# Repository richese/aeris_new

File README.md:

# aeris_new
aeris mutirobtics system

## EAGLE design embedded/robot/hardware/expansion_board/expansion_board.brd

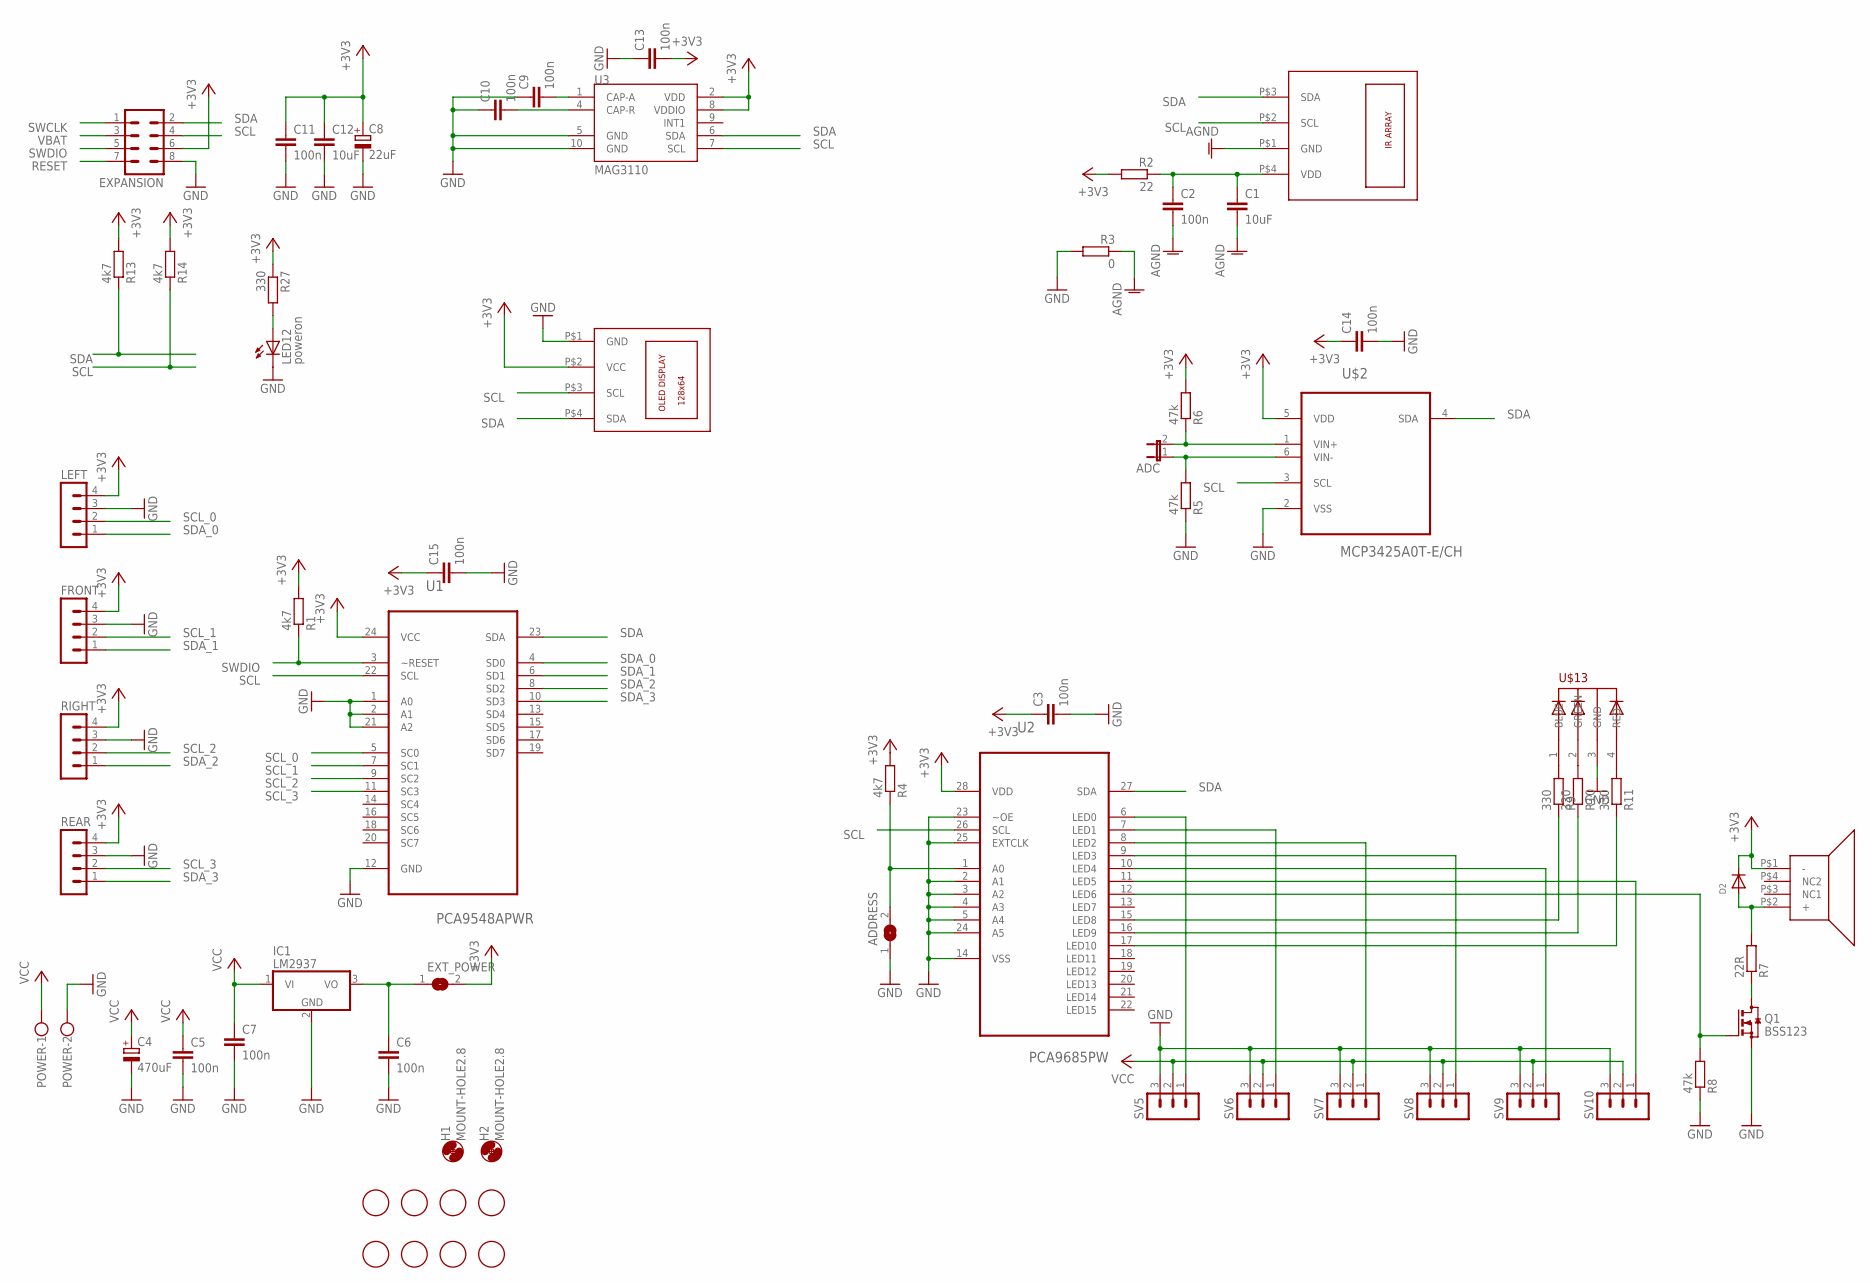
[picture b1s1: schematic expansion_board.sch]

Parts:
ADC: JP1E; JP1
ADDRESS: SJ
C1, C12: 10uF; C0805
C2, C3, C5, C6, C7, C9, C10, C11, C13, C14, C15: 100n; C0805
C4: 470uF; 153CLV-1012
C8: 22uF; 153CLV-0505
D2: DIODE_SOD-123FL; SOD-123FL
EXPANSION: MA04-2
EXT_POWER: SJ
FRONT: MA04-1
H1, H2: MOUNT-HOLE2.8; 2,8
IC1: LM2937; TO263-3
LED12: poweron; CHIPLED_1206
LEFT: MA04-1
POWER: W237-102
Q1: BSS123; SOT23
R1, R4, R13, R14: 4k7; M0805
R2: 22; M0805
R3: 0; M0805
R5, R6, R8: 47k; M0805
R7: 22R; M0805
R9, R10, R11, R27: 330; M0805
REAR: MA04-1
RIGHT: MA04-1
SV5, SV6, SV7, SV8, SV9, SV10: MA03-1
U1: PCA9548APWR; SOP65P640X120-24N
U2: PCA9685PW; SOP65P640X110-28N
U3: MAG3110; DFN-10
U$1: MLX90621
U$2: MCP3425A0T-E/CH; SOT95P270X145-6N
U$3: SPEAKER_KAAG15008C; KAAG15008C
U$4: OLED_DISPLAY_096_INCH
U$5, U$6, U$7, U$8, U$9, U$10, U$11, U$12: FIDUCIAL; FIDUCIAL_1MM
U$13: 5MMRGBLED; LED5MMRGB

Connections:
+3V3: C3.1, C8.+, C11.1, C12.1, C13.2, C14.1, C15.1, D2.C, EXPANSION.6, EXT_POWER.2, FRONT.4, LEFT.4, R1.2, R2.2, R4.2, R6.2, R13.2, R14.2, R27.1, REAR.4, RIGHT.4, U1.24 (VCC), U2.28 (VDD), U3.2 (VDD), U3.8 (VDDIO), U$2.5 (VDD), U$3.P$1 (-), U$4.P$2 (VCC)
AGND: C1.2, C2.2, R3.1, U$1.P$1 (GND)
GND: ADDRESS.1, C3.2, C4.-, C5.2, C6.2, C7.2, C8.-, C9.1, C10.1, C11.2, C12.2, C13.1, C14.2, C15.2, EXPANSION.8, FRONT.3, IC1.2 (GND), LED12.C, LEFT.3, POWER.2, Q1.2 (S), R3.2, R5.1, R8.1, REAR.3, RIGHT.3, SV5.3, SV6.3, SV7.3, SV8.3, SV9.3, SV10.3, U1.1 (A0), U1.2 (A1), U1.12 (GND), U1.21 (A2), U2.2 (A1), U2.3 (A2), U2.4 (A3), U2.5 (A4), U2.14 (VSS), U2.23 (~OE), U2.24 (A5), U2.25 (EXTCLK), U3.5 (GND), U3.10 (GND), U$2.2 (VSS), U$4.P$1 (GND), U$13.3 (GND)
unnamed: C1.1, C2.1, R2.1, U$1.P$4 (VDD)
unnamed: SV5.1, U2.6 (LED0)
unnamed: SV6.1, U2.7 (LED1)
unnamed: SV7.1, U2.8 (LED2)
unnamed: SV8.1, U2.9 (LED3)
unnamed: SV9.1, U2.10 (LED4)
unnamed: SV10.1, U2.11 (LED5)
unnamed: C6.1, EXT_POWER.1, IC1.3 (VO)
unnamed: ADDRESS.2, R4.1, U2.1 (A0)
unnamed: C9.2, U3.1 (CAP-A)
unnamed: C10.2, U3.4 (CAP-R)
unnamed: ADC.1, R5.2, U$2.6 (VIN-)
unnamed: ADC.2, R6.1, U$2.1 (VIN+)
unnamed: R9.2, U$13.1 (BLUE)
unnamed: Q1.1 (G), R8.2, U2.12 (LED6)
unnamed: Q1.3 (D), R7.1
unnamed: D2.A, R7.2, U$3.P$2 (+)
unnamed: R11.2, U$13.4 (RED)
unnamed: R10.2, U$13.2 (GREEN)
unnamed: LED12.A, R27.2
unnamed: R9.1, U2.15 (LED8)
unnamed: R10.1, U2.16 (LED9)
unnamed: R11.1, U2.17 (LED10)
RESET: EXPANSION.7
SCL: EXPANSION.4, R14.1, U1.22 (SCL), U2.26 (SCL), U3.7 (SCL), U$1.P$2 (SCL), U$2.3 (SCL), U$4.P$3 (SCL)
SCL_0: LEFT.2, U1.5 (SC0)
SCL_1: FRONT.2, U1.7 (SC1)
SCL_2: RIGHT.2, U1.9 (SC2)
SCL_3: REAR.2, U1.11 (SC3)
SDA: EXPANSION.2, R13.1, U1.23 (SDA), U2.27 (SDA), U3.6 (SDA), U$1.P$3 (SDA), U$2.4 (SDA), U$4.P$4 (SDA)
SDA_0: LEFT.1, U1.4 (SD0)
SDA_1: FRONT.1, U1.6 (SD1)
SDA_2: RIGHT.1, U1.8 (SD2)
SDA_3: REAR.1, U1.10 (SD3)
SWCLK: EXPANSION.1
SWDIO: EXPANSION.5, R1.1, U1.3 (~RESET)
VBAT: EXPANSION.3
VCC: C4.+, C5.1, C7.1, IC1.1 (VI), POWER.1, SV5.2, SV6.2, SV7.2, SV8.2, SV9.2, SV10.2

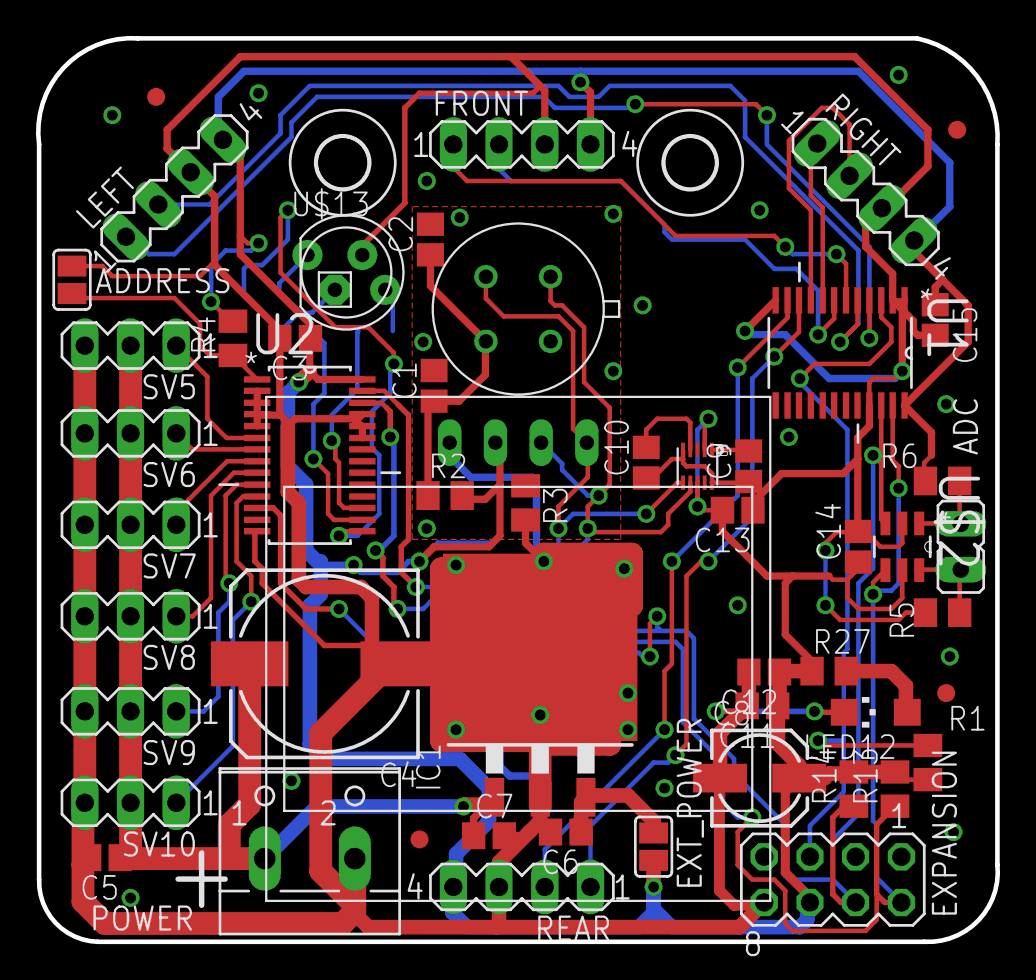
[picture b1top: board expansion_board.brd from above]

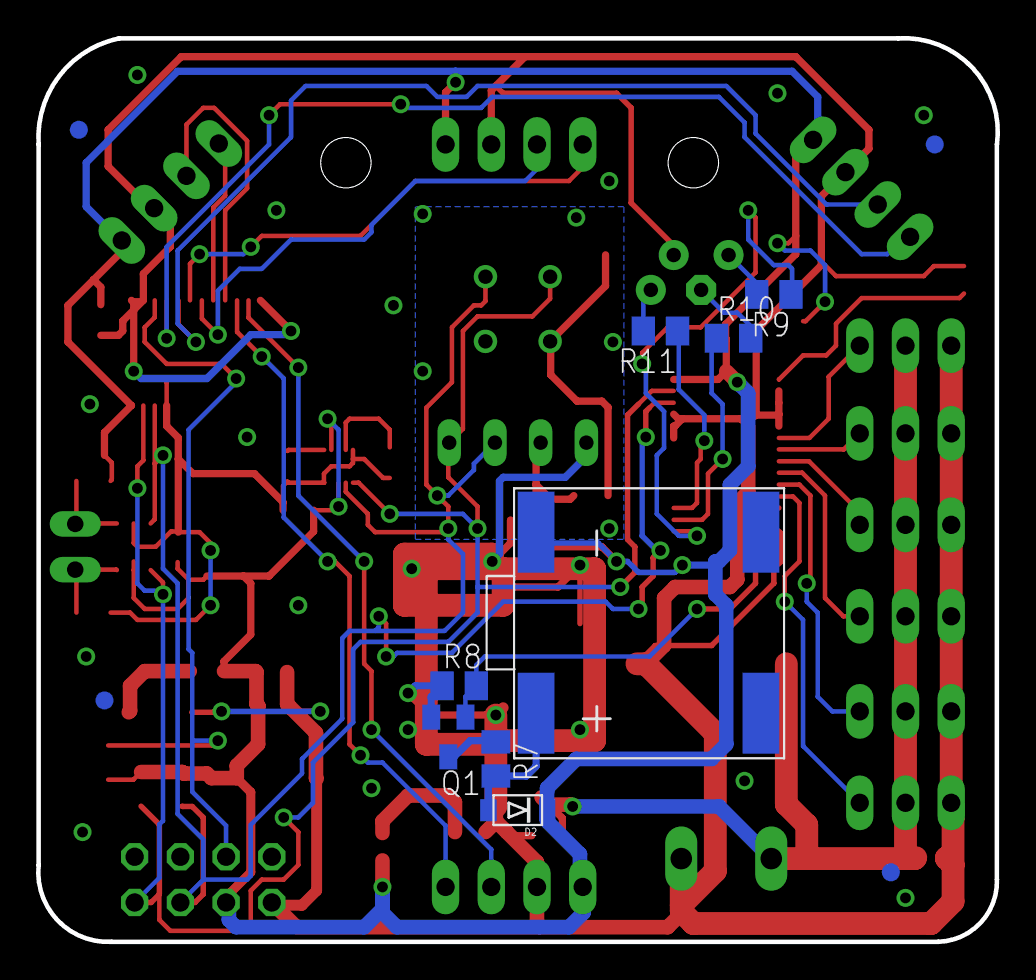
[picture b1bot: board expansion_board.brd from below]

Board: 2 copper layers, 53.3 x 50.2 mm, 66 parts (12 on the bottom side), 38 nets.

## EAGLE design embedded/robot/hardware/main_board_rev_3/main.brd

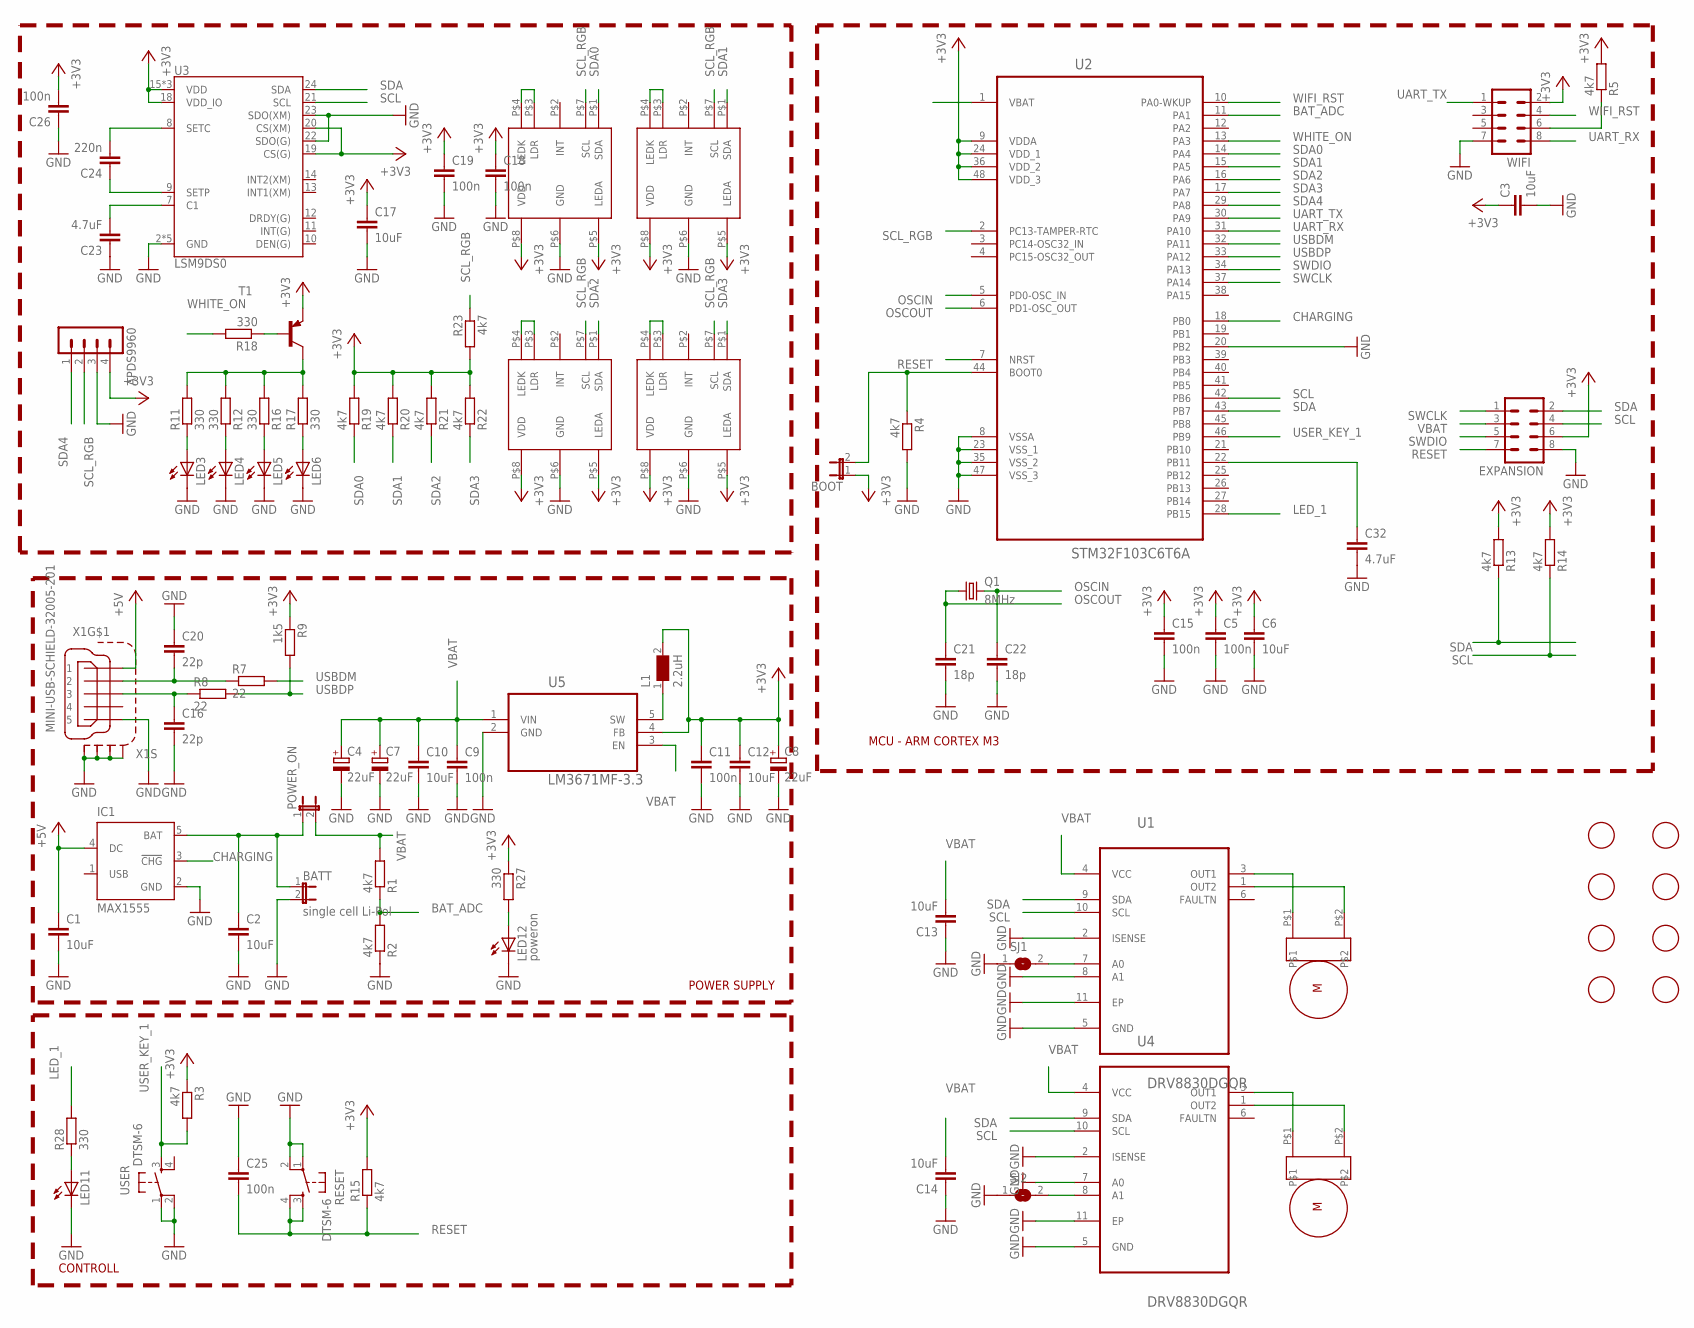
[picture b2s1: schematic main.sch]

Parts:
APDS9960: MA04-1
BATT: single cell Li-Pol; JP1
BOOT: JP1E; JP1
C1, C2, C3, C6, C10, C12, C13, C14, C17: 10uF; C0805
C4, C7, C8: 22uF; 153CLV-0505
C5, C9, C11, C15, C18, C19, C25, C26: 100n; C0805
C16, C20: 22p; C0805
C21, C22: 18p; C0805
C23, C32: 4.7uF; C0805
C24: 220n; C0805
EXPANSION: MA04-2
IC1: MAX1555; SOT23-5L
L1: 2.2uH; WE-LQ_M
LED3, LED4, LED5, LED6, LED11: LEDCHIPLED_1206; CHIPLED_1206
LED12: poweron; CHIPLED_1206
POWER_ON: JP1E; JP1
Q1: 8MHz; CTS406
R1, R2, R4, R5, R13, R14, R15, R19, R20, R21, R22, R23: 4k7; M0805
R3: 4k7; M1206
R7, R8: 22; M0805
R9: 1k5; M0805
R11, R12, R16, R17, R18, R27, R28: 330; M0805
RESET: DTSM-6
SJ1, SJ2: SJ
T1: BC857A-PNP-SOT23-BEC; SOT23-BEC
U1, U4: DRV8830DGQR; SOP65P640X110-15N
U2: STM32F103C6T6A; QFP50P900X900X160-48N
U3: LSM9DS0; LGA-24
U5: LM3671MF-3.3; SOT95P284X122-5N
U$1, U$2, U$3, U$4: APDS9950
U$5, U$6: MICRO_METAL_GEAR_MOTOR
U$9, U$10, U$11, U$12, U$13, U$14, U$15, U$16: FIDUCIAL; FIDUCIAL_1MM
USER: DTSM-6
WIFI: MA04-2
X1: MINI-USB-SCHIELD-32005-201; 32005-201

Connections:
+3V3: APDS9960.4, BOOT.1, C3.1, C5.1, C6.1, C8.+, C11.1, C12.1, C15.1, C17.1, C18.1, C19.1, C26.2, EXPANSION.6, L1.2, R3.1, R5.2, R9.1, R13.2, R14.2, R15.2, R19.2, R20.2, R21.2, R22.2, R23.2, R27.1, T1.E, U2.9 (VDDA), U2.24 (VDD_1), U2.36 (VDD_2), U2.48 (VDD_3), U3.15 (VDD), U3.16 (VDD), U3.17 (VDD), U3.18 (VDD_IO), U3.19 (CS(G)), U3.20 (CS(XM)), U5.4 (FB), U$1.P$5 (LEDA), U$1.P$8 (VDD), U$2.P$5 (LEDA), U$2.P$8 (VDD), U$3.P$5 (LEDA), U$3.P$8 (VDD), U$4.P$5 (LEDA), U$4.P$8 (VDD), WIFI.2
+5V: C1.1, IC1.4 (DC), X1.1
BAT_ADC: R1.1, R2.2, U2.11 (PA1)
CHARGING: IC1.3 (!CHG), U2.18 (PB0)
GND: APDS9960.3, BATT.2, C1.2, C2.2, C3.2, C4.-, C5.2, C6.2, C7.-, C8.-, C9.2, C10.2, C11.2, C12.2, C13.1, C14.1, C15.2, C16.2, C17.2, C18.2, C19.2, C20.1, C21.2, C22.2, C23.1, C25.1, C26.1, C32.2, EXPANSION.8, IC1.2 (GND), LED3.C, LED4.C, LED5.C, LED6.C, LED11.C, LED12.C, R2.1, R4.2, RESET.1, RESET.2, SJ1.1, SJ2.1, U1.2 (ISENSE), U1.5 (GND), U1.8 (A1), U1.11 (EP), U2.8 (VSSA), U2.20 (PB2), U2.23 (VSS_1), U2.35 (VSS_2), U2.47 (VSS_3), U3.2 (GND), U3.3 (GND), U3.4 (GND), U3.5 (GND), U3.6 (GND), U3.22 (SDO(G)), U3.23 (SDO(XM)), U4.2 (ISENSE), U4.5 (GND), U4.7 (A0), U4.11 (EP), U5.2 (GND), U$1.P$6 (GND), U$2.P$6 (GND), U$3.P$6 (GND), U$4.P$6 (GND), USER.1, USER.2, WIFI.7, X1.5, X1.M1 (S1), X1.M2 (S2), X1.M3 (S3), X1.M4 (S4)
LED_1: R28.2, U2.28 (PB15)
unnamed: R5.1, WIFI.6
unnamed: BATT.1, C2.1, IC1.5 (BAT), POWER_ON.1
unnamed: U1.1 (OUT2), U$5.P$2
unnamed: U1.3 (OUT1), U$5.P$1
unnamed: U4.1 (OUT2), U$6.P$2
unnamed: C23.2, U3.7 (C1)
unnamed: C24.2, U3.8 (SETC)
unnamed: U4.3 (OUT1), U$6.P$1
unnamed: L1.1, U5.5 (SW)
unnamed: C24.1, U3.9 (SETP)
unnamed: C32.1, U2.22 (PB11)
unnamed: LED3.A, R11.1
unnamed: BOOT.2, R4.1, U2.44 (BOOT0)
unnamed: U$1.P$3 (LDR), U$1.P$4 (LEDK)
unnamed: U$2.P$3 (LDR), U$2.P$4 (LEDK)
unnamed: U$3.P$3 (LDR), U$3.P$4 (LEDK)
unnamed: U$4.P$3 (LDR), U$4.P$4 (LEDK)
unnamed: SJ1.2, U1.7 (A0)
unnamed: LED4.A, R12.1
unnamed: LED12.A, R27.2
unnamed: LED5.A, R16.1
unnamed: LED6.A, R17.1
unnamed: R11.2, R12.2, R16.2, R17.2, T1.C
unnamed: R18.1, T1.B
unnamed: SJ2.2, U4.8 (A1)
unnamed: LED11.A, R28.1
unnamed: C20.2, R7.1, X1.2
unnamed: C16.1, R8.1, X1.3
NC: U2.1 (VBAT)
OSCIN: C22.1, Q1.3 (2), U2.5 (PD0-OSC_IN)
OSCOUT: C21.1, Q1.1, U2.6 (PD1-OSC_OUT)
RESET: C25.2, EXPANSION.7, R15.1, RESET.3, RESET.4, U2.7 (NRST)
SCL: EXPANSION.4, R14.1, U1.10 (SCL), U2.42 (PB6), U3.21 (SCL), U4.10 (SCL)
SCL_RGB: APDS9960.2, R23.1, U2.2 (PC13-TAMPER-RTC), U$1.P$7 (SCL), U$2.P$7 (SCL), U$3.P$7 (SCL), U$4.P$7 (SCL)
SDA: EXPANSION.2, R13.1, U1.9 (SDA), U2.43 (PB7), U3.24 (SDA), U4.9 (SDA)
SDA0: R19.1, U2.14 (PA4), U$1.P$1 (SDA)
SDA1: R20.1, U2.15 (PA5), U$2.P$1 (SDA)
SDA2: R21.1, U2.16 (PA6), U$3.P$1 (SDA)
SDA3: R22.1, U2.17 (PA7), U$4.P$1 (SDA)
SDA4: APDS9960.1, U2.29 (PA8)
SWCLK: EXPANSION.1, U2.37 (PA14)
SWDIO: EXPANSION.5, U2.34 (PA13)
UART_RX: U2.31 (PA10), WIFI.8
UART_TX: U2.30 (PA9), WIFI.1
USBDM: R7.2, U2.32 (PA11)
USBDP: R8.2, R9.2, U2.33 (PA12)
USER_KEY_1: R3.2, U2.46 (PB9), USER.3
VBAT: C4.+, C7.+, C9.1, C10.1, C13.2, C14.2, EXPANSION.3, POWER_ON.2, R1.2, U1.4 (VCC), U4.4 (VCC), U5.1 (VIN), U5.3 (EN)
WHITE_ON: R18.2, U2.13 (PA3)
WIFI_RST: U2.10 (PA0-WKUP), WIFI.4

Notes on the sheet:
POWER SUPPLY
CONTROLL
MCU - ARM CORTEX M3

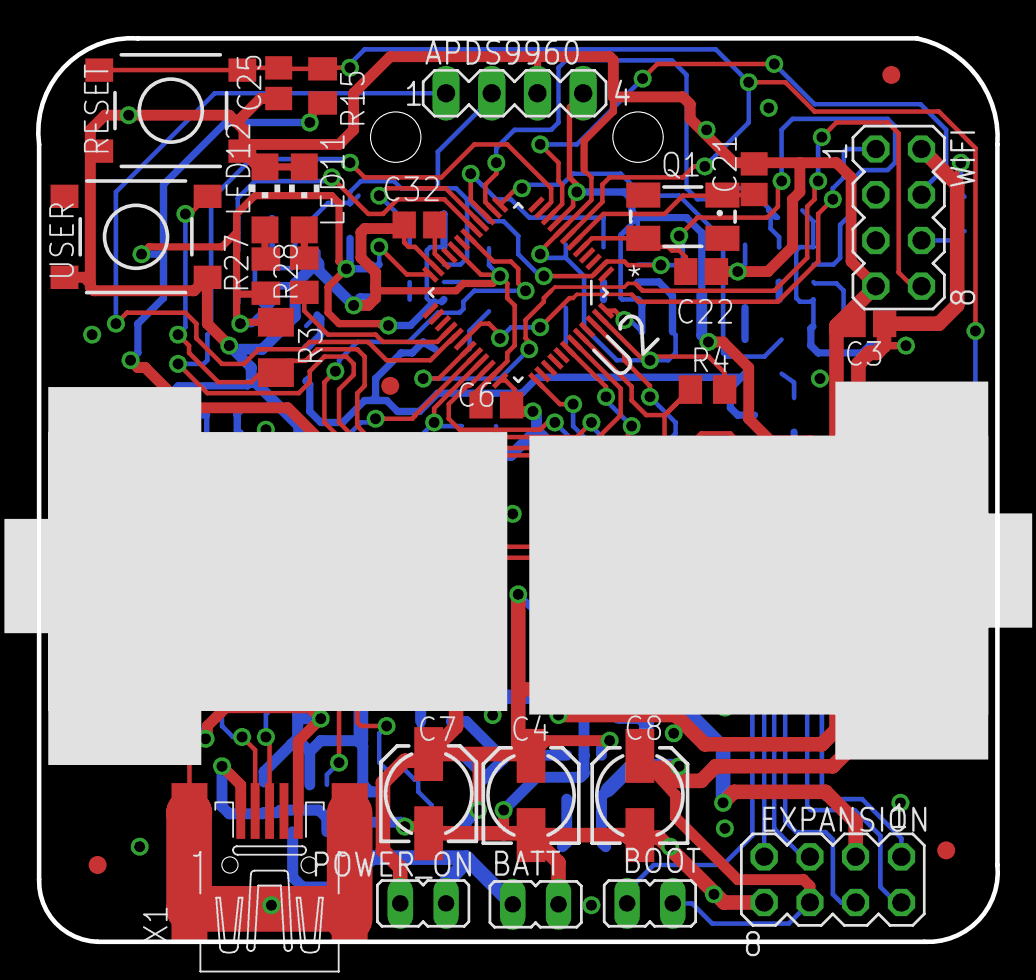
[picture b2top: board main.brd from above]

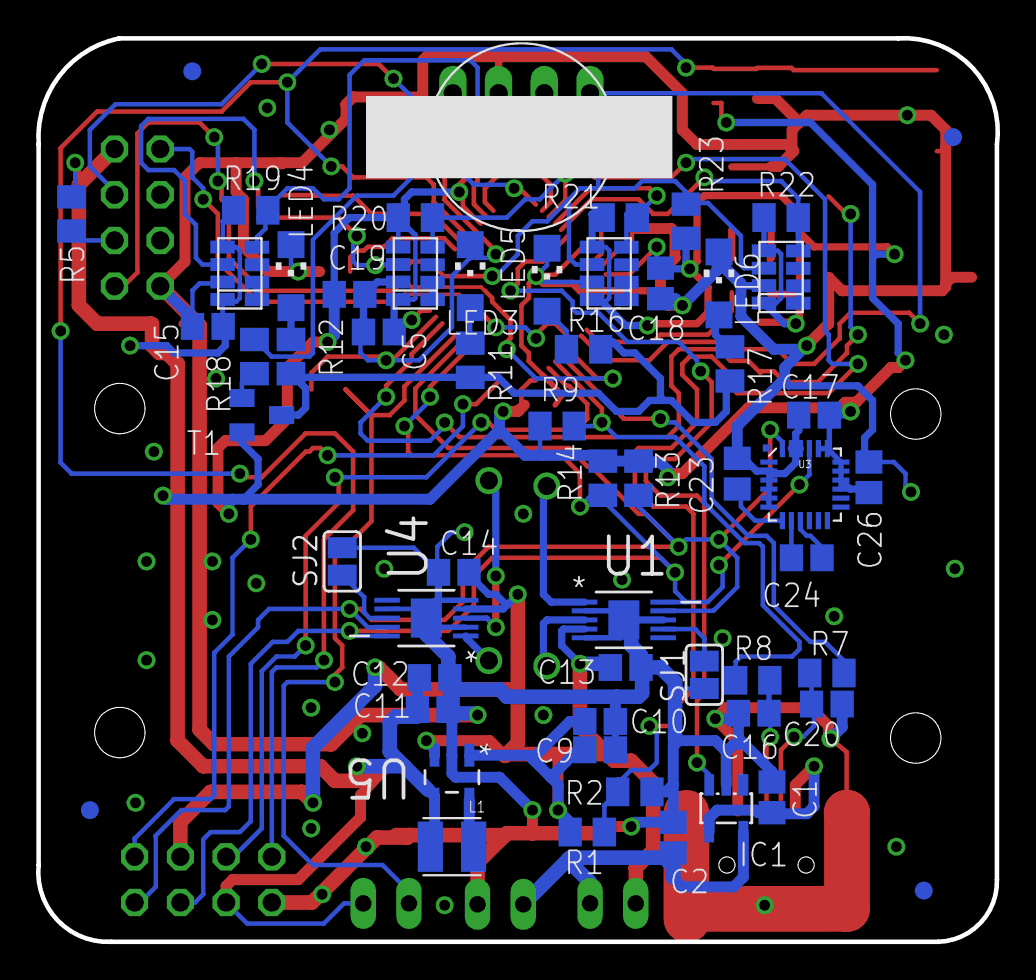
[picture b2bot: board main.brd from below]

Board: 2 copper layers, 53.3 x 50.2 mm, 92 parts (59 on the bottom side), 55 nets.

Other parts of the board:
U$7: BALL_3/8
U$8: LOGO_SMALL_BMP

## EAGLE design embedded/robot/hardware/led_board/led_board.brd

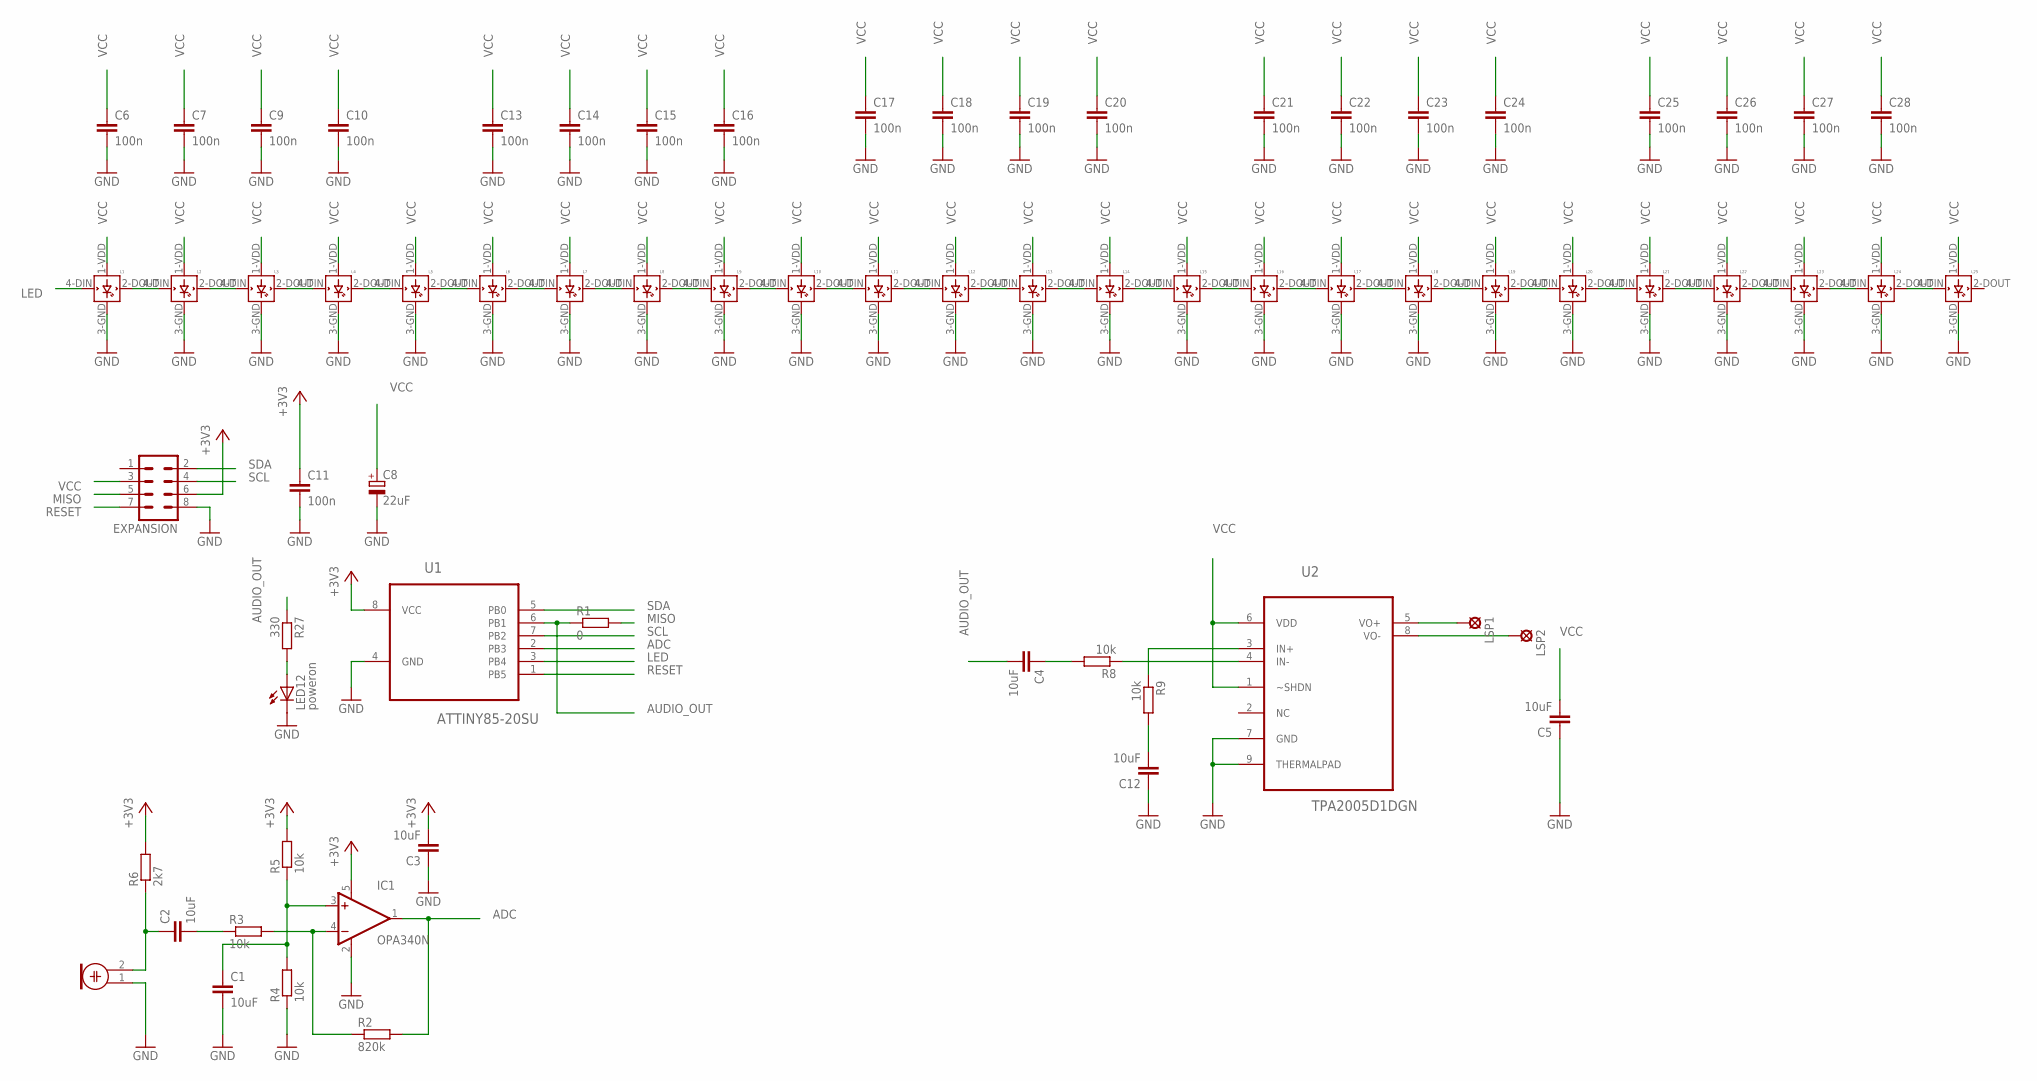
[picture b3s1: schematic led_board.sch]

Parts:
C1, C2, C3, C4, C5, C12: 10uF; C0805
C6, C7, C9, C10, C11, C13, C14, C15, C16, C17, C18, C19, C20, C21, C22, C23, C24, C25, C26, C27, C28: 100n; C0805
C8: 22uF; 153CLV-0505
EXPANSION: MA04-2
IC1: OPA340N; SOT23-5
L1, L2, L3, L4, L5, L6, L7, L8, L9, L10, L11, L12, L13, L14, L15, L16, L17, L18, L19, L20, L21, L22, L23, L24, L25: WS2812B
LED12: poweron; CHIPLED_1206
LSP1, LSP2: LSP10
M1: ELECTRET_MICROPHON-WM-61B; WM-61B
R1: 0; M0805
R2: 820k; M0805
R3, R4, R5, R8, R9: 10k; M0805
R6: 2k7; M0805
R27: 330; M0805
U1: ATTINY85-20SU; SOIC127P798X216-8N
U2: TPA2005D1DGN; SOP65P488X107-9N

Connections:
+3V3: C3.2, C11.1, EXPANSION.6, IC1.5 (V+), R5.2, R6.2, U1.8 (VCC)
ADC: IC1.1 (OUT), R2.2, U1.2 (PB3)
AUDIO_OUT: C4.2, R1.1, R27.1, U1.6 (PB1)
GND: C1.2, C3.1, C5.1, C6.2, C7.2, C8.-, C9.2, C10.2, C11.2, C12.1, C13.2, C14.2, C15.2, C16.2, C17.2, C18.2, C19.2, C20.2, C21.2, C22.2, C23.2, C24.2, C25.2, C26.2, C27.2, C28.2, EXPANSION.8, IC1.2 (V-), L1.3-GND (GND), L2.3-GND (GND), L3.3-GND (GND), L4.3-GND (GND), L5.3-GND (GND), L6.3-GND (GND), L7.3-GND (GND), L8.3-GND (GND), L9.3-GND (GND), L10.3-GND (GND), L11.3-GND (GND), L12.3-GND (GND), L13.3-GND (GND), L14.3-GND (GND), L15.3-GND (GND), L16.3-GND (GND), L17.3-GND (GND), L18.3-GND (GND), L19.3-GND (GND), L20.3-GND (GND), L21.3-GND (GND), L22.3-GND (GND), L23.3-GND (GND), L24.3-GND (GND), L25.3-GND (GND), LED12.C, M1.1, R4.1, U1.4 (GND), U2.7 (GND), U2.9 (THERMALPAD)
LED: L1.4-DIN (DIN), U1.3 (PB4)
LED1: L5.2-DOUT (DOUT), L6.4-DIN (DIN)
LED2: L15.2-DOUT (DOUT), L16.4-DIN (DIN)
LED3: L20.2-DOUT (DOUT), L21.4-DIN (DIN)
MISO: EXPANSION.5, R1.2
unnamed: L1.2-DOUT (DOUT), L2.4-DIN (DIN)
unnamed: L2.2-DOUT (DOUT), L3.4-DIN (DIN)
unnamed: L3.2-DOUT (DOUT), L4.4-DIN (DIN)
unnamed: L4.2-DOUT (DOUT), L5.4-DIN (DIN)
unnamed: LSP1.MP, U2.5 (VO+)
unnamed: L6.2-DOUT (DOUT), L7.4-DIN (DIN)
unnamed: L7.2-DOUT (DOUT), L8.4-DIN (DIN)
unnamed: L8.2-DOUT (DOUT), L9.4-DIN (DIN)
unnamed: L9.2-DOUT (DOUT), L10.4-DIN (DIN)
unnamed: L11.2-DOUT (DOUT), L12.4-DIN (DIN)
unnamed: L12.2-DOUT (DOUT), L13.4-DIN (DIN)
unnamed: L13.2-DOUT (DOUT), L14.4-DIN (DIN)
unnamed: L14.2-DOUT (DOUT), L15.4-DIN (DIN)
unnamed: L16.2-DOUT (DOUT), L17.4-DIN (DIN)
unnamed: L17.2-DOUT (DOUT), L18.4-DIN (DIN)
unnamed: L18.2-DOUT (DOUT), L19.4-DIN (DIN)
unnamed: L19.2-DOUT (DOUT), L20.4-DIN (DIN)
unnamed: L10.2-DOUT (DOUT), L11.4-DIN (DIN)
unnamed: L21.2-DOUT (DOUT), L22.4-DIN (DIN)
unnamed: LED12.A, R27.2
unnamed: L22.2-DOUT (DOUT), L23.4-DIN (DIN)
unnamed: L23.2-DOUT (DOUT), L24.4-DIN (DIN)
unnamed: L24.2-DOUT (DOUT), L25.4-DIN (DIN)
unnamed: C2.2, R3.1
unnamed: IC1.4 (-IN), R2.1, R3.2
unnamed: C2.1, M1.2, R6.1
unnamed: C1.1, IC1.3 (+IN), R4.2, R5.1
unnamed: R8.1, U2.4 (IN-)
unnamed: LSP2.MP, U2.8 (VO-)
unnamed: C4.1, R8.2
unnamed: C12.2, R9.2
unnamed: R9.1, U2.3 (IN+)
RESET: EXPANSION.7, U1.1 (PB5)
SCL: EXPANSION.4, U1.7 (PB2)
SDA: EXPANSION.2, U1.5 (PB0)
VCC: C5.2, C6.1, C7.1, C8.+, C9.1, C10.1, C13.1, C14.1, C15.1, C16.1, C17.1, C18.1, C19.1, C20.1, C21.1, C22.1, C23.1, C24.1, C25.1, C26.1, C27.1, C28.1, EXPANSION.3, L1.1-VDD (VDD), L2.1-VDD (VDD), L3.1-VDD (VDD), L4.1-VDD (VDD), L5.1-VDD (VDD), L6.1-VDD (VDD), L7.1-VDD (VDD), L8.1-VDD (VDD), L9.1-VDD (VDD), L10.1-VDD (VDD), L11.1-VDD (VDD), L12.1-VDD (VDD), L13.1-VDD (VDD), L14.1-VDD (VDD), L15.1-VDD (VDD), L16.1-VDD (VDD), L17.1-VDD (VDD), L18.1-VDD (VDD), L19.1-VDD (VDD), L20.1-VDD (VDD), L21.1-VDD (VDD), L22.1-VDD (VDD), L23.1-VDD (VDD), L24.1-VDD (VDD), L25.1-VDD (VDD), U2.1 (~SHDN), U2.6 (VDD)

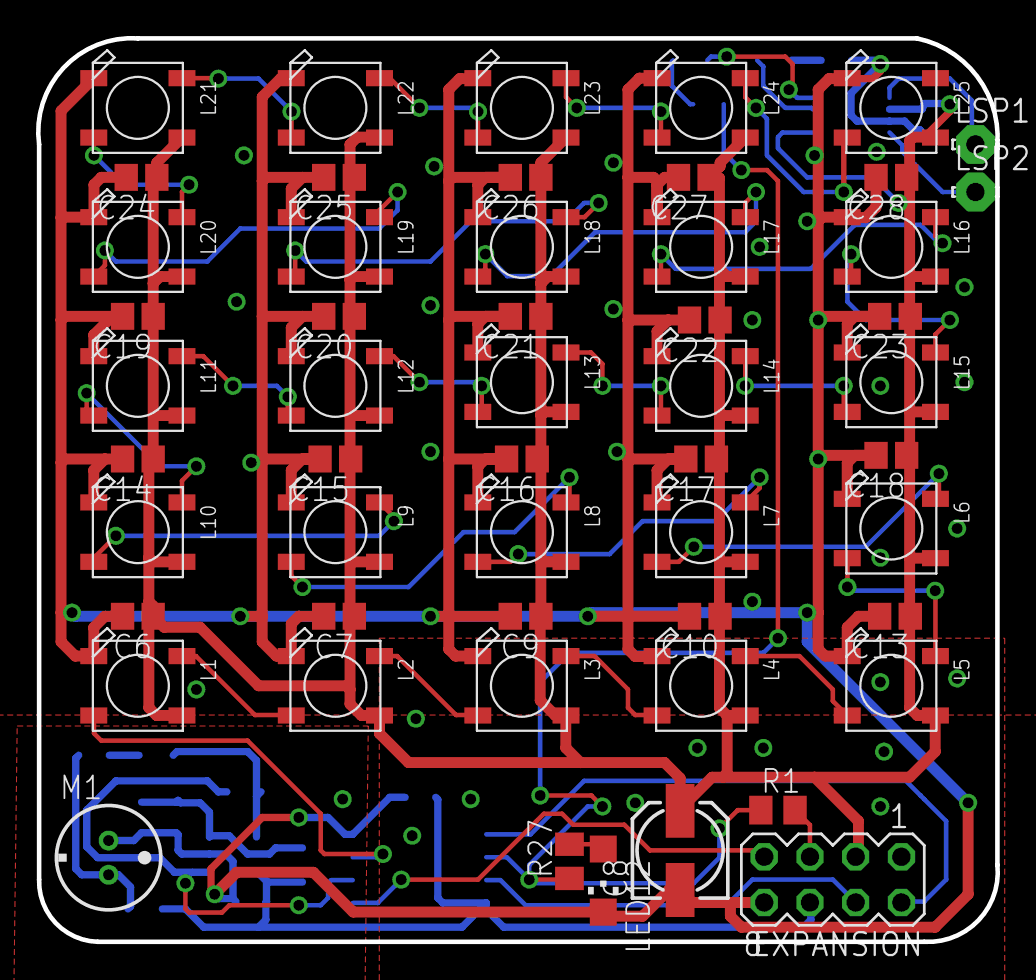
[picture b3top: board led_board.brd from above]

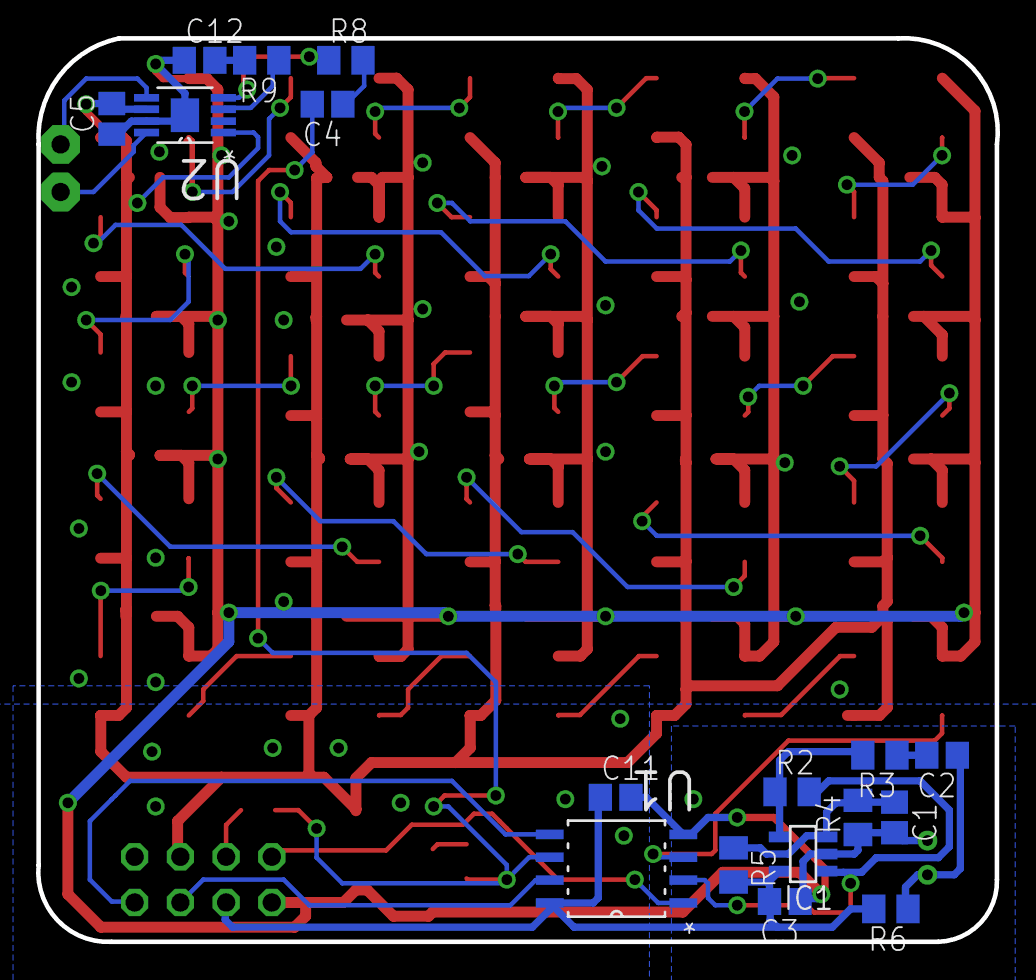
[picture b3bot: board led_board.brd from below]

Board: 2 copper layers, 53.3 x 50.2 mm, 70 parts (17 on the bottom side), 45 nets.

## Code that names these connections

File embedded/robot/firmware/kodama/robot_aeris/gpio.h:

#ifndef _GPIO_H_
#define _GPIO_H_

#include <stdint.h>

#define LED_0		(1<<15)    //main led, PB15
#define LED_1		(1<<3)    //white led for sensors ilumination, PA3
#define KEY 		(1<<9)    //main button, PB9

#define ENCODER_CONSTANT ((uint32_t)750) //670


class CGPIO
{
  public:
    CGPIO();
    ~CGPIO();

    int32_t gpio_init();

    void gpio_on(uint32_t pin);
    void gpio_off(uint32_t pin);
    uint32_t gpio_in(uint32_t pin);

    int32_t get_left_encoder();
    int32_t get_right_encoder();
    int32_t get_encoder_distance();

  public:
    void led_blinking_init();
    void led_blinking_set_pwm(unsigned int pwm);
    void led_blinking(unsigned int mode);
};


#endif

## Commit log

2016-10-02 real time class added
2016-10-04 common
2016-10-04 serialization
2016-10-04 client part done
2016-10-05 obj_loader
2016-10-05 obj loaded
2016-10-06 first version done
2016-10-06 visualisation added
2016-10-06 mess cleaned up
2016-10-07 pheromones added
2016-10-07 done
2016-10-07 config changes
2016-10-08 ant added
2016-10-09 ant colony added
2016-10-11 uint64
2016-10-11 client bug removed
2016-10-12 Added unix domain socket support.
2016-10-12 Fix server waiting for thread.
2016-10-12 Better run script.
2016-11-03 line bot addeded
2016-11-03 screen size changed
2016-11-06 Terminantion signal handler added.
2016-11-08 run script
2016-11-10 Meson build system.
    Homepage: https://github.com/mesonbuild/meson
    Ubuntu package: apt-get install meson
2016-11-11 Cleanup server and server socket code. Add easyloggingc++ to handle logs.
2016-11-11 Cleaned up client side socket code. Added loging to line demo related agents.
2016-11-12 Updated rest of agents.
2016-11-12 Added performance tracking. More log coverage.
2016-11-12 Add comments to scripts. Fix trailing whitespaces.
2016-11-13 Fix client not falling back to AF_INET socket connection. Check for dependencies in build scripts.
2016-11-14 Added mutex to SocketWatch
2016-11-24 Ported line agent from old system.
2016-11-29 robot firmware added
2016-12-12 wifi added
2016-12-14 i_led added :blush:
2016-12-20 some boards changes
2016-12-21 mode slector added :monkey: - need fltk gui library
2016-12-21 robot bridge - first commit
2016-12-22 AgentBody memory managment.
2016-12-22 debug app
2016-12-22 debug app gui works :smile:
2016-12-24 robot bridge gui
2017-01-09 expansion board
2017-01-18 Client-server communication performance refactor done.
2017-01-18 Rename agents folder to plugins.
2017-01-19 Code refactor.
2017-01-19 Remove commited binaries
2017-01-19 thread creating problem solved
2017-01-19 Remove debugging messages.
2017-02-04 Override library install directory. (needed for Ubuntu systems)
2017-02-05 Added checkpoint support to performance log parser.
2017-02-28 Added border body. Added ba-demo script.
2017-04-28 Fix server crash when client commits agents with discontinuous ids.
2017-04-28 Skip file path resolution for absolute paths.
2017-04-28 Separate client side communication interface from AgentGroup to standalone class.
2017-04-30 Border is now part of VisualisationAgent and is drawn if "border_width" parameter is set to positive value. Unit of "border_width" is cm.
2017-04-30 Camera robot tracking code.
2017-04-30 Allow the use of custom agent type for tracked robots. Fix color format conversion for tracked robots.
2017-05-04 Fix multithreaded agent processing.
2017-05-04 Containers used for agent creation in plugins are now returned by value.
2017-05-05 Make visualisation plugin optional based on found system dependencies.
2017-05-05 Test moving initialization around.
2017-05-12 Build environment now prefers local installations of meson and ninja. Change default dynamic library load policy to RTLD_NOW.
2017-05-14 Fix border not being drawn over agents.
2017-05-14 Fix log parser not converting seconds to milliseconds.
2017-05-16 Fix robot-tracking not returning when started with invalid arguments. Fix Segmentator ignoring FAST threshold value set by config.
2017-06-22 Disable `expansion-to-defined` warning added to gcc. It spams warnings from elpp.
2017-06-24 Remove unneeded vector allocation. Scoping takes care of it.
2017-06-24 Updated JSON library to v2.1.1
2017-06-25 Added doxyfile to generate doxygen documentation. Added robot tracking class documentation.
2017-06-25 Moved misc types to separate header. Unified some class names: * sAgentPosition -> AgentPosition * sColor -> Color * sAgentInterface -> AgentInterface
2017-06-25 Refector of shared agent body storage.
2017-06-26 Redesign of plugins.

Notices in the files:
parts and their libraries:
SparkFun-Sensors: Licensing: Creative Commons ShareAlike 4.0 International - https://creativecommons.org/licenses/by-sa/4.0
